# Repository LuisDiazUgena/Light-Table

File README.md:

# Light-Table

Light Table design files & Firmware

##Arduino shield

###Regulated version

Arduino shield drives from 12V DC Jack (Center positive) and power Arduino through a voltage regulator (LM7805/Murata 7805SRH-C) with decoupling caps. Works with pwm to control Mosfets (IRF3205) (Up to 1.2A/Mosfet).

**If using Murata 7805SRH-C do not use decoupling caps, there is no need for it.**

### Non regulated version

Power the whole thing with 12V connected on the DC Jack of the shield (**Do not connect other jack on the board**). If your board is a cheap clone or you are not sure that it got a good regulator or protection, use regulated version.

##Arduino Firmware

Support single or long click: Single click put FW in color selection mode and long click clears the leds.
Control color over Bluetooth and Android/Protocoder App.

##Android Apps
###Protocoder

Protocoder app is used to control color on the light table over Bluetooth. You can download both code and project from Android apps folder.

###App Inventor

App Inventor app is used to control color on the light table over Bluetooth. You can download both code and project from Android apps folder.

##Hardware Used

<table>
  <tr>
    <th class="tg-031e">Reference</th>
    <th class="tg-031e">Value</th>
  </tr>
  <tr>
    <td class="tg-031e">C1</td>
    <td class="tg-031e">100uF</td>
  </tr>
  <tr>
    <td class="tg-031e">C2</td>
    <td class="tg-031e">10uF</td>
  </tr>
  <tr>
    <td class="tg-031e">CON1</td>
    <td class="tg-031e">BARREL_JACK</td>
  </tr>
  <tr>
    <td class="tg-031e">D1</td>
    <td class="tg-031e">PWR</td>
  </tr>
  <tr>
    <td class="tg-031e">EN1</td>
    <td class="tg-031e">ENCODER_5_PINS</td>
  </tr>
  <tr>
    <td class="tg-031e">P1</td>
    <td class="tg-031e">Screw Block 2</td>
  </tr>
  <tr>
    <td class="tg-031e">P8</td>
    <td class="tg-031e">Screw Block 4</td>
  </tr>
  <tr>
    <td class="tg-031e">R1</td>
    <td class="tg-031e">10K</td>
  </tr>
  <tr>
    <td class="tg-031e">R2</td>
    <td class="tg-031e">330</td>
  </tr>
  <tr>
    <td class="tg-031e">SHIELD1</td>
    <td class="tg-031e">ARDUINO_SHIELD</td>
  </tr>
  <tr>
    <td class="tg-031e">U1</td>
    <td class="tg-031e">IRF3205</td>
  </tr>
  <tr>
    <td class="tg-031e">U2</td>
    <td class="tg-031e">IRF3205</td>
  </tr>
  <tr>
    <td class="tg-031e">U3</td>
    <td class="tg-031e">IRF3205</td>
  </tr>
  <tr>
    <td class="tg-031e">U4</td>
    <td class="tg-031e">LM7805</td>
  </tr>
</table>

##Issues

### 1: Inefficient power regulation (n = 0.41667).

Generates so much heat. Solutions:

1. Change Lm7805 module to 78XXSR Murata switching regulator.
2. Add a Heatsink (Still to much heat) and a fan.

By using a efficient power regulation will not need to use heat sink and/or fan.

Will change LM7805 module to a 7805SRH-C module. efficiency graph:

As it will have 12V as input voltage will get from 87 to 90% efficiency.

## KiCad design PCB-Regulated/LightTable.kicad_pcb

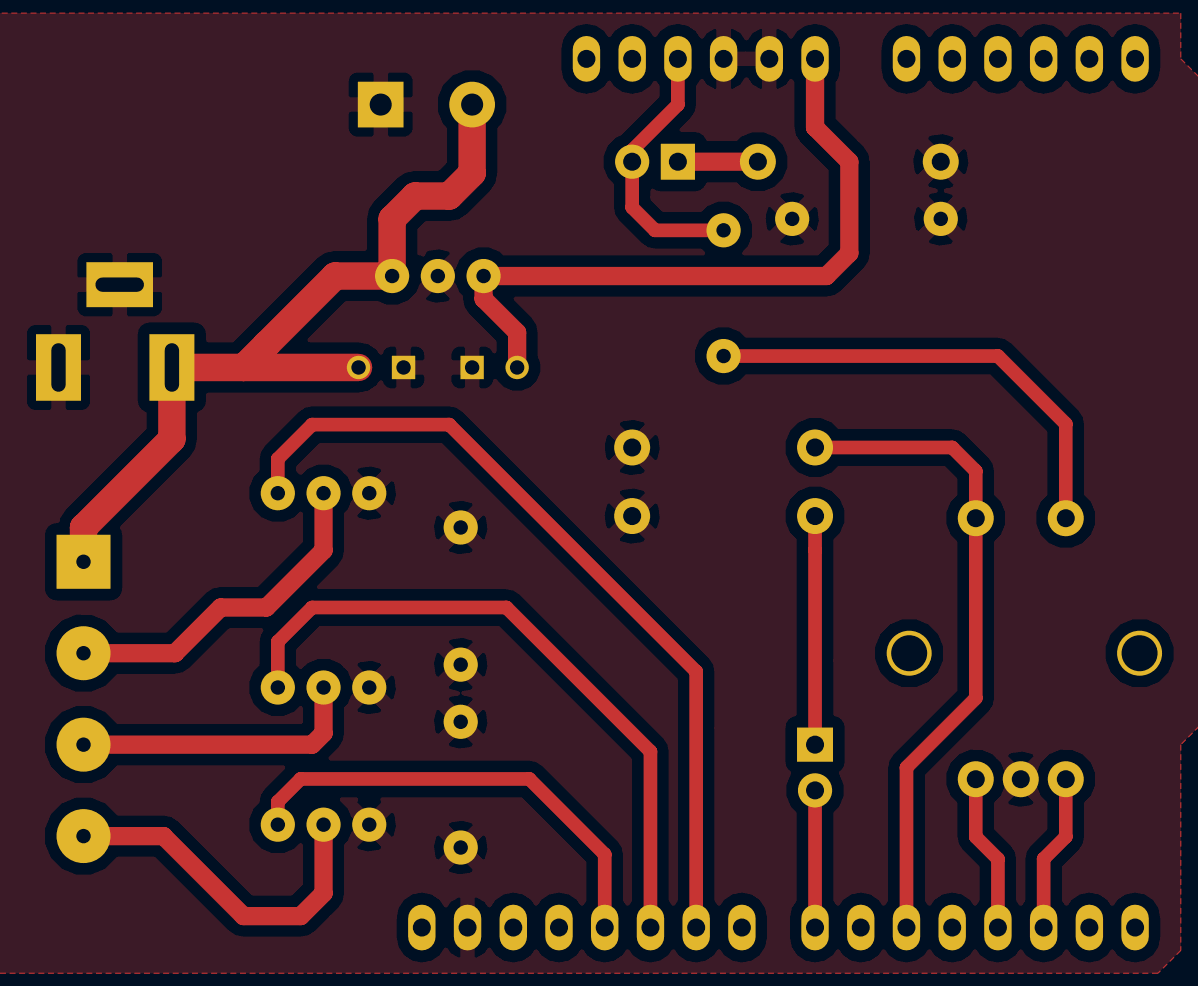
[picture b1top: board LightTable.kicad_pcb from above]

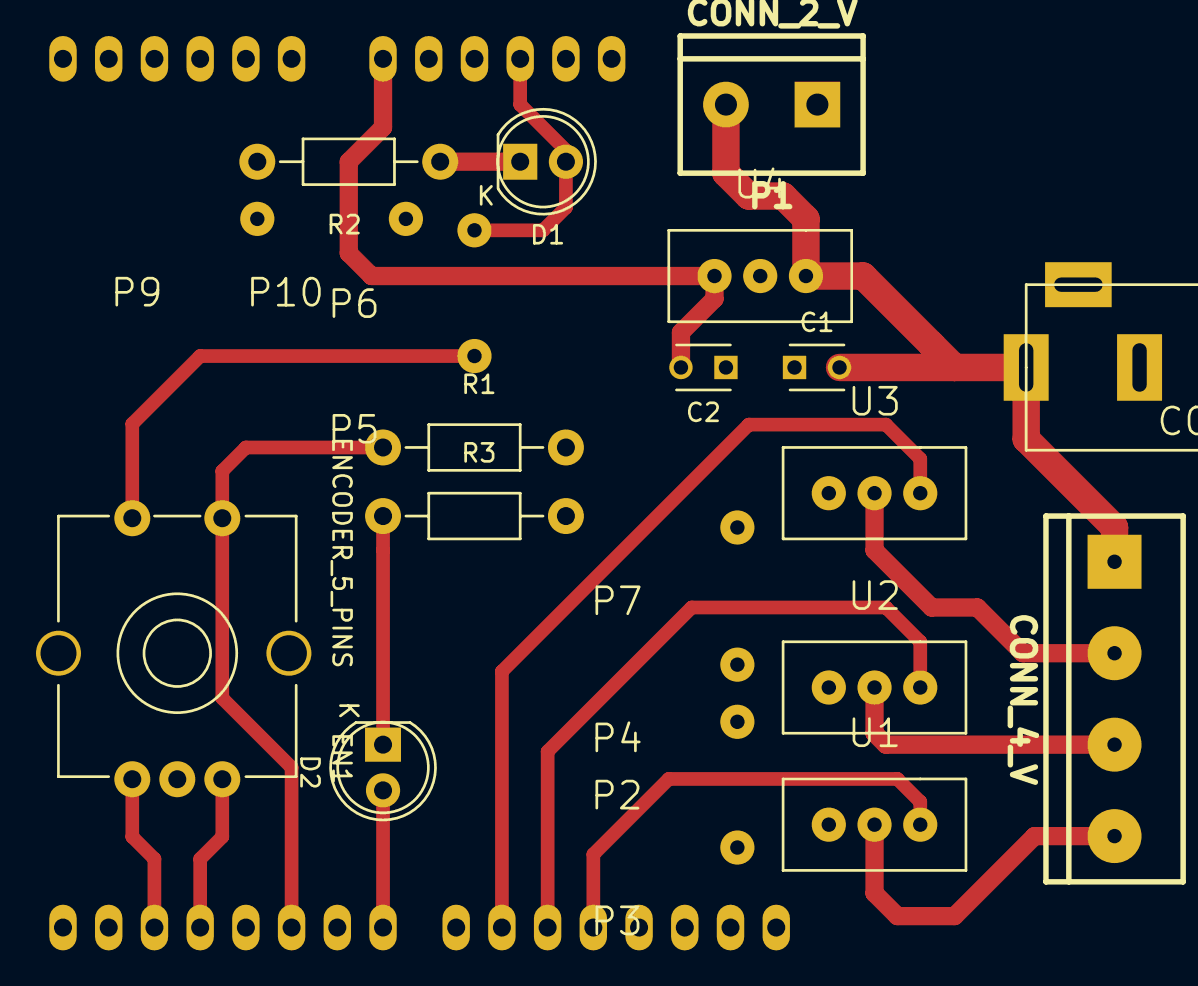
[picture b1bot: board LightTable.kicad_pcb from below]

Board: 2 copper layers, 24 parts (24 on the bottom side), 16 nets.

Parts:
C1: 100uF; C_Disc_D3_P2.5
C2: 10uF; C_Disc_D3_P2.5
CON1: BARREL_JACK
D1: PWR; LED-5MM
D2: Long; LED-5MM
EN1: ENCODER_5_PINS
P1: CONN_2_V; bornier2_V
P2, P3, P4, P5, P6, P7, P9, P10: CONN_01X01; header1x01
P8: CONN_4_V; bornier4_V
R1: 10K; Resistor_Horizontal_RM10mm
R2, R3: 330; Resistor_Horizontal_RM10mm
SHIELD1: ARDUINO_SHIELD; ARDUINO_SHIELD_2_040pins
U1, U2, U3: MosfetIRF; IRF3205
U4: LM7805

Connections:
+12V: C1.2, CON1.1, P1.2, P8.4, U4.VI
B: P8.3, U3.2
G: P8.2, U2.2
GND: C1.1, C2.1, CON1.2, CON1.3, EN1.2, P1.1, P2.1, P3.1, P4.1, P7.1, P9.1, P10.1, R1.2, R2.2, R3.2, SHIELD1.GND1, SHIELD1.GND2, SHIELD1.GND3, U1.3, U2.3, U3.3, U4.GND
unnamed: D1.1, R2.1
unnamed: D2.1, R3.1
unnamed: D2.2, SHIELD1.7
unnamed: EN1.1, SHIELD1.3
unnamed: EN1.3, SHIELD1.2
PBtn: EN1.5, R1.1, SHIELD1.5
PWM_B: SHIELD1.9, U3.1
PWM_G: SHIELD1.10, U2.1
PWM_R: SHIELD1.11, U1.1
R: P8.1, U1.2
V5: C2.2, SHIELD1.V_IN, U4.VO
VCC: D1.2, EN1.4, P5.1, P6.1, SHIELD1.5V

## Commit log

2015-06-19 Initial FW of lightTable
2015-06-19 changed trimmer pin to free XTAL pins to add a 16MHz crystal
2015-06-19 Added schematich, attiny and icsp libraries
2015-08-12 Added SfSerial
2015-08-12 Working on a shield
2015-08-13 Added pcb layout and libraries
2015-08-13 Moved encoder to .pretty folder
2015-08-13 Added Power Led and BOM
2015-08-13 Added info about shield, FW and HW
2015-08-13 Added image of pcb layout
2015-08-13 Fixed error with html table
2015-08-13 Added svg file
2015-08-13 Added support for encoder. Started working on led control
2015-08-13 Added led support
2015-08-13 Added long click support
2015-08-13 Remove println info or moved into debug
2015-08-13 Updated FW info
2015-08-14 Added support for Bluetooth
2015-08-14 Added Protocoder App & code
2015-08-14 Changed folder name
2015-08-14 Updated info about last changes
2015-08-14 Added App Inventor project & apk
2015-08-14 Changed name of Pallete Elements
2015-08-14 Added long click for turning on/off the leds
2015-08-17 Fixed bug-after a long click doesn't turn off
2015-08-17 Changed capacitor values
2015-08-17 Added issues info
2015-08-17 Added led for showing when a long click has been made
2015-08-17 Added info about efficiency of 78xx module
2015-08-17 minor changes
2015-08-18 Added links to special parts used
2015-08-18 Created shield that uses voltage regulator in the board
2015-08-18 Added info about pcb versions
2015-08-20 Fixed wrong placement of shield and added gerbers
2015-08-20 Changed pads to oval shape
2015-08-20 Fixed wrong placement of shield
2015-08-20 Added GND jumper to improve ground connectivity
2015-08-25 Added gerbers
2015-08-25 improved pads
